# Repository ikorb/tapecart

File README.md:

# Tapecart SD #

This is a fork of tapecart that adds SD card support using the Tapuino hardware.
TCRT, PRG, and P00 files can be loaded using the Tapecart SD Browser (browser.prg) which should be placed in the root directory of the SD card.

Tapecart SD is not intended as a replacement for the Tapuino firmware, as there are no support for buttons and display
or using TAP files. Ideally, I would have preferred to use the original tapecart hardware and just replaced the SPI flash
with a SD card reader. However, the program flash in the microcontroller is too small for the FatFs library.

Flash and loader write commands are supported for TCRT files.

## Hardware ##

The Tapecart SD firmware should work on any Tapuino hardware.
For the tapecart LED this can be connected to the PD2 pin which is normally not used on a Tapuino.

There is also also this special version without buttons and display made for the Tapecart SD by CapFuture1975.
The gerber files for that version can be found under [hardware/Tapecart-SD](hardware/Tapecart-SD)

# tapecart #

tapecart - a tape port storage pod for the C64

Copyright (C) 2013-2017 by Ingo Korb <ingo@akana.de>
All rights reserved.
Idea by enthusi

# About #

The tapecart is a low-cost flash storage device for the Commodore 64's
tape port. This repository contains source code and documentation
related to it and will one day contain the schematics and layout files too.

# Structure of the repository #

This repository is organized as follows:

* doc

    This directory contains general documentation regarding the
    tapecart like the protocol it uses to communicate with the C64.

* src-c64

    This directory contains the source code for the C64-side
    software, currently the initial loader and the flashtool.

* sd_browser

    This directory contains the source code for the Tapecart SD Browser.

* src-firmware

    This directory contains the source code for the firmware running
    on the tapecart.

* hardware

    This directory contains schematics and layout for various hardware
    variants of the tapecart.

* mass-programmer

    This directory contains schematics, layout and software for a
    Raspberry Pi addon board that can be used for mass-programming
    tapecarts.

Schematics and layout for the tapecart itself will be released at a
later date.

# License #

The firmware itself is distributed under the following conditions:

    Redistribution and use in source and binary forms, with or without
    modification, are permitted provided that the following conditions
    are met:
    1. Redistributions of source code must retain the above copyright
       notice, this list of conditions and the following disclaimer.
    2. Redistributions in binary form must reproduce the above copyright
       notice, this list of conditions and the following disclaimer in the
       documentation and/or other materials provided with the distribution.

    THIS SOFTWARE IS PROVIDED BY THE REGENTS AND CONTRIBUTORS ``AS IS'' AND
    ANY EXPRESS OR IMPLIED WARRANTIES, INCLUDING, BUT NOT LIMITED TO, THE
    IMPLIED WARRANTIES OF MERCHANTABILITY AND FITNESS FOR A PARTICULAR PURPOSE
    ARE DISCLAIMED.  IN NO EVENT SHALL THE REGENTS OR CONTRIBUTORS BE LIABLE
    FOR ANY DIRECT, INDIRECT, INCIDENTAL, SPECIAL, EXEMPLARY, OR CONSEQUENTIAL
    DAMAGES (INCLUDING, BUT NOT LIMITED TO, PROCUREMENT OF SUBSTITUTE GOODS
    OR SERVICES; LOSS OF USE, DATA, OR PROFITS; OR BUSINESS INTERRUPTION)
    HOWEVER CAUSED AND ON ANY THEORY OF LIABILITY, WHETHER IN CONTRACT, STRICT
    LIABILITY, OR TORT (INCLUDING NEGLIGENCE OR OTHERWISE) ARISING IN ANY WAY
    OUT OF THE USE OF THIS SOFTWARE, EVEN IF ADVISED OF THE POSSIBILITY OF
    SUCH DAMAGE.

Please note that the firmware source code includes third-party header files
taken from the Atmel Software Framework. Please check its
[README](src-firmware/README.md) for more details.

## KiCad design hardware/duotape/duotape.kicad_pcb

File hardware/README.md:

# tapecart hardware #

This directory contains KiCAD schematics and layout for three
different implementations of the tapecart:

* DIY

    This version of the tapecart is optimized for DIY builders - it
    does not require any SMD components. Since DIP versions of the
    flash chips are a bit hard to source, it has an alternate
    footprint for using an SMD flash chip instead. The firmware for
    this version must be compiled using the config file "config-diy".
    A precompiled hex file is located in the subdirectory "firmware".

* SMD-Onesided-R1 and SMD-Twosided-R1

    These two versions of the tapecart are optimized for cost, using
    SMD components. Both are electrically the same, but one of them
    saves a bit more board space by placing components on both sides
    of the board. The firmware for both of these versions must be
    compiled using the config file "config-release1". A precompiled
    binary is located in the subdirectory "firmware".

* duotape and duotape-riser

    A simple tapecart-compatible tapeport switch, e.g. to switch
    between two tapecarts or a tapecart and a Datasette(-emulator).
    duotape is the main switch PCB, duotape-riser contains a layout
    for a really trivial adapter board in case you don't have a 3.96mm
    stripboard available.
    
# Tapecart SD hardware #

* Tapecart-SD

    A simple version of the Tapuino hardware without buttons and display
    specially made for Tapecart SD by CapFuture1975.

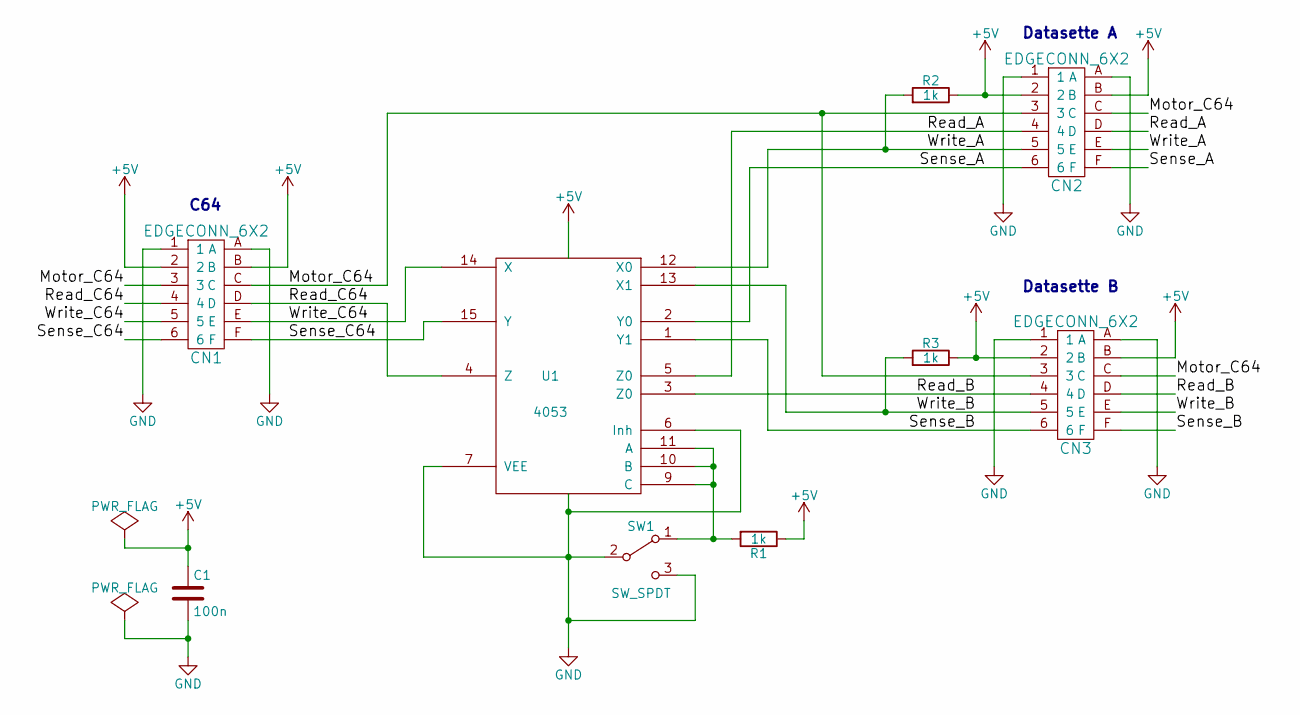
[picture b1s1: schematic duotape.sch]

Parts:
C1: 100n; C_Rect_L7_W2_P5
CN1, CN2: EDGECONN_6X2; EDGECONN_6x2_IMP
CN3: EDGECONN_6X2; VERTCONN_6X2
R1, R2, R3: 1k; Resistor_Horizontal_RM10mm
SW1: SW_SPDT; Switch_TL36P0
U1: 4053; DIP-16_W7.62mm

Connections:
+5V: C1.1, CN1.2, CN1.B, CN2.2, CN2.B, CN3.2, CN3.B, R1.1, R2.1, R3.1, U1.16 (VDD)
/Motor_C64: CN1.3, CN1.C, CN2.3, CN2.C, CN3.3, CN3.C
/Read_A: CN2.4, CN2.D, U1.5 (Z0)
/Read_B: CN3.4, CN3.D, U1.3 (Z0)
/Read_C64: CN1.4, CN1.D, U1.4 (Z)
/Sense_A: CN2.6, CN2.F, U1.2 (Y0)
/Sense_B: CN3.6, CN3.F, U1.1 (Y1)
/Sense_C64: CN1.6, CN1.F, U1.15 (Y)
/Write_A: CN2.5, CN2.E, R2.2, U1.12 (X0)
/Write_B: CN3.5, CN3.E, R3.2, U1.13 (X1)
/Write_C64: CN1.5, CN1.E, U1.14 (X)
GND: C1.2, CN1.1, CN1.A, CN2.1, CN2.A, CN3.1, CN3.A, SW1.2 (B), SW1.3 (C), U1.6 (Inh), U1.7 (VEE), U1.8 (VSS)
unnamed: R1.2, SW1.1 (A), U1.9 (C), U1.10 (B), U1.11 (A)

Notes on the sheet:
C64
Datasette A
Datasette B

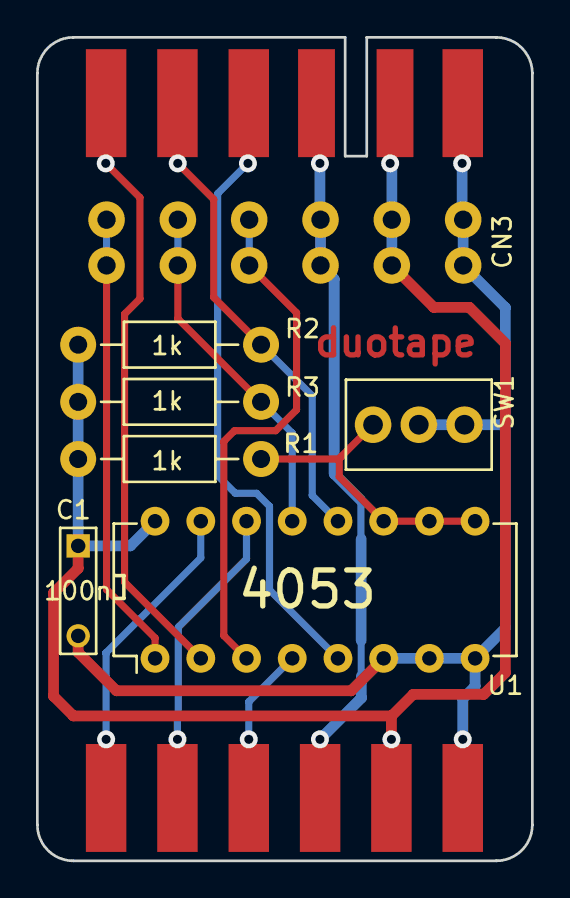
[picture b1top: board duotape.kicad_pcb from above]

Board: 2 copper layers, 27.5 x 45.8 mm, 9 parts (0 on the bottom side), 13 nets.

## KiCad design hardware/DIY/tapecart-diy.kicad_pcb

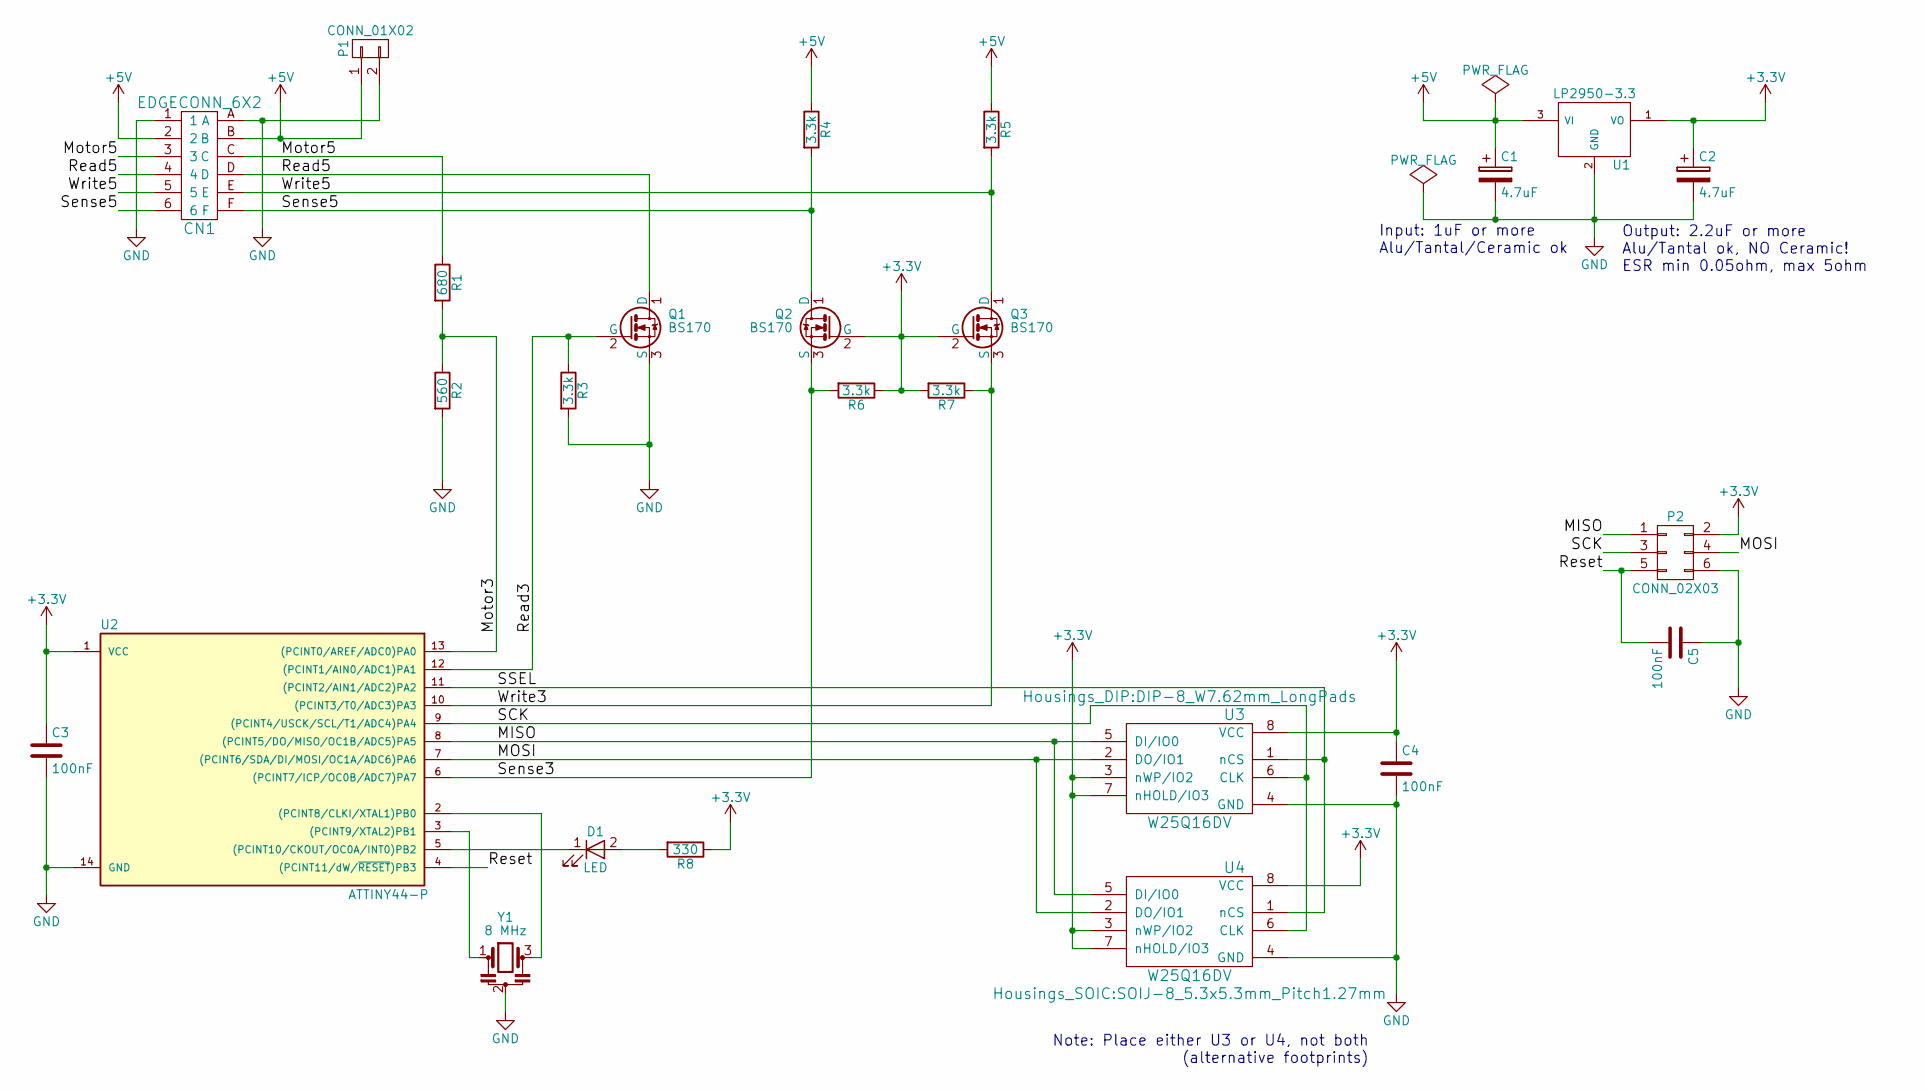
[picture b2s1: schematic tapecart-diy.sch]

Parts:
C1, C2: 4.7uF; C_Radial_D5_L11_P2
C3, C4, C5: 100nF; C_Disc_D3_P2.5
CN1: EDGECONN_6X2; EDGECONN_6x2_IMP_5mm
D1: LED; LED-3MM
P1: CONN_01X02; Pin_Header_Straight_1x02
P2: CONN_02X03; Pin_Header_Straight_2x03
Q1, Q2, Q3: BS170; TO-92_Inline_Wide
R1: 680; Resistor_Horizontal_RM10mm
R2: 560; Resistor_Horizontal_RM10mm
R3, R4, R5, R6, R7: 3.3k; Resistor_Horizontal_RM10mm
R8: 330; Resistor_Horizontal_RM10mm
U1: LP2950-3.3; TO-92_Inline_Wide
U2: ATTINY44-P; DIP-14_W7.62mm_LongPads
U3: W25Q16DV; DIP-8_W7.62mm_LongPads
U4: W25Q16DV; SOIJ-8_5.3x5.3mm_Pitch1.27mm
Y1: 8 MHz; Pin_Header_Straight_1x03

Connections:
+3V3: C2.1, C3.1, C4.1, P2.2, Q2.2 (G), Q3.2 (G), R6.1, R7.2, R8.1, U1.1 (VO), U2.1 (VCC), U3.3 (nWP/IO2), U3.7 (nHOLD/IO3), U3.8 (VCC), U4.3 (nWP/IO2), U4.7 (nHOLD/IO3), U4.8 (VCC)
+5V: C1.1, CN1.2, CN1.B, P1.1, R4.1, R5.1, U1.3 (VI)
/MISO: P2.1, U2.8 ((PCINT5/DO/MISO/OC1B/ADC5)PA5), U3.5 (DI/IO0), U4.5 (DI/IO0)
/MOSI: P2.4, U2.7 ((PCINT6/SDA/DI/MOSI/OC1A/ADC6)PA6), U3.2 (DO/IO1), U4.2 (DO/IO1)
/Motor3: R1.2, R2.1, U2.13 ((PCINT0/AREF/ADC0)PA0)
/Motor5: CN1.3, CN1.C, R1.1
/Read3: Q1.2 (G), R3.1, U2.12 ((PCINT1/AIN0/ADC1)PA1)
/Read5: CN1.4, CN1.D, Q1.1 (D)
/Reset: C5.2, P2.5, U2.4 ((PCINT11/dW/~RESET~)PB3)
/SCK: P2.3, U2.9 ((PCINT4/USCK/SCL/T1/ADC4)PA4), U3.6 (CLK), U4.6 (CLK)
/SSEL: U2.11 ((PCINT2/AIN1/ADC2)PA2), U3.1 (nCS), U4.1 (nCS)
/Sense3: Q2.3 (S), R6.2, U2.6 ((PCINT7/ICP/OC0B/ADC7)PA7)
/Sense5: CN1.6, CN1.F, Q2.1 (D), R4.2
/Write3: Q3.3 (S), R7.1, U2.10 ((PCINT3/T0/ADC3)PA3)
/Write5: CN1.5, CN1.E, Q3.1 (D), R5.2
GND: C1.2, C2.2, C3.2, C4.2, C5.1, CN1.1, CN1.A, P1.2, P2.6, Q1.3 (S), R2.2, R3.2, U1.2 (GND), U2.14 (GND), U3.4 (GND), U4.4 (GND), Y1.2
unnamed: D1.1 (K), U2.5 ((PCINT10/CKOUT/OC0A/INT0)PB2)
unnamed: D1.2 (A), R8.2
unnamed: U2.2 ((PCINT8/CLKI/XTAL1)PB0), Y1.3
unnamed: U2.3 ((PCINT9/XTAL2)PB1), Y1.1

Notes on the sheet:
Input: 1uF or more Alu/Tantal/Ceramic ok
Output: 2.2uF or more Alu/Tantal ok, NO Ceramic! ESR min 0.05ohm, max 5ohm
Note: Place either U3 or U4, not both (alternative footprints)

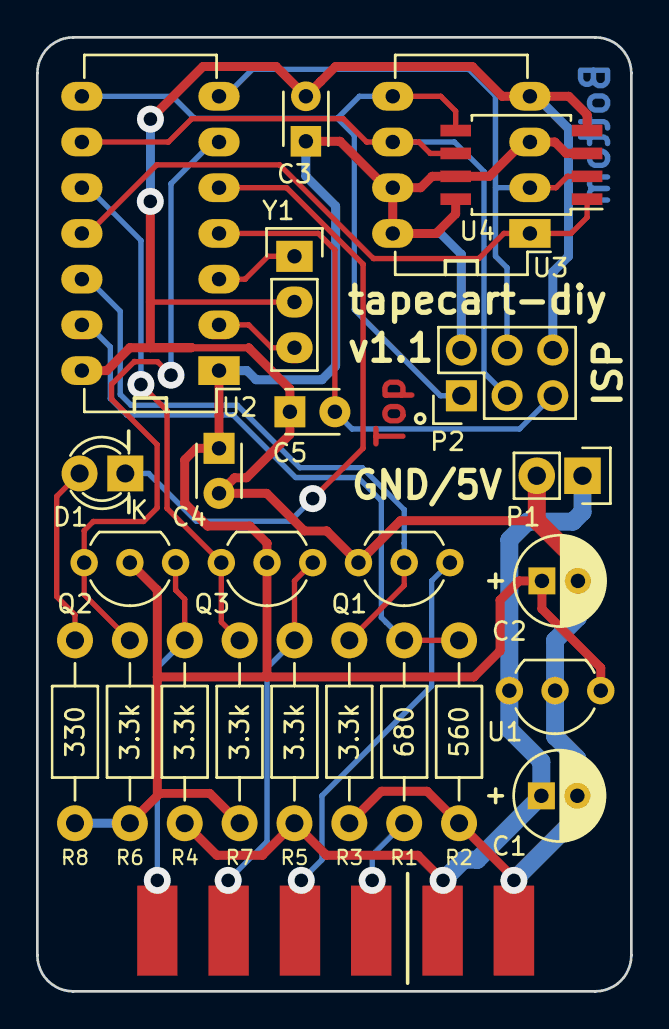
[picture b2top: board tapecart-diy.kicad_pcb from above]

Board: 2 copper layers, 33.0 x 53.0 mm, 25 parts (0 on the bottom side), 20 nets.

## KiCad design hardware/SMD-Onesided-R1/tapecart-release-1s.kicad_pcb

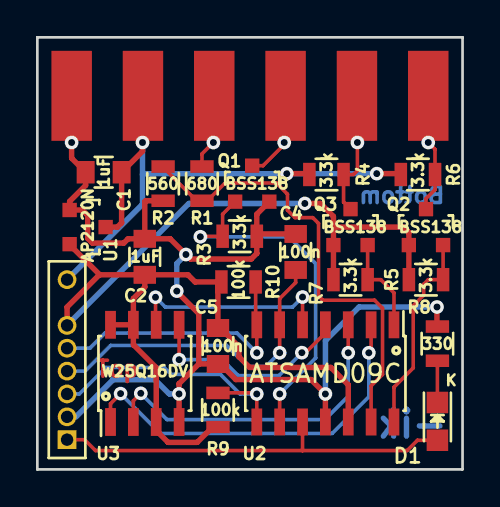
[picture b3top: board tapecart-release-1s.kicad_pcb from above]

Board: 2 copper layers, 23.6 x 24.0 mm, 23 parts (0 on the bottom side), 20 nets.

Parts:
C1, C2: 1uF; C_0805
C4, C5: 100n; C_0805
CN1: EDGECONN_6X2; EDGECONN_6x2_IMP_5mm
CN2: CONN_01X07; PINHEAD_6p1X1_1.27
D1: LED; LED_0805
Q1, Q2, Q3: BSS138; SOT-23
R1: 680; R_0805
R2: 560; R_0805
R3, R4, R5, R6, R7: 3.3k; R_0805
R8: 330; R_0805
R9, R10: 100k; R_0805
U1: AP2120N; SOT-23
U2: ATSAMD09C; SOIC-14_3.9x8.7mm_Pitch1.27mm
U3: W25Q16DV; SOIC-8_3.9x4.9mm_Pitch1.27mm

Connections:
+3V3: C2.1, C5.1, CN2.6, Q2.1, Q3.1, R5.1, R7.2, R9.1, R10.1, U1.2, U2.12, U3.3, U3.7, U3.8
+5V: C1.1, CN1.2, CN1.B, CN2.7, R4.1, R6.1, U1.3
/LED: CN2.1, D1.2, U2.10
/MISO: U2.3, U3.2
/MOSI: U2.4, U3.5
/Motor3: R1.2, R2.1, U2.13
/Motor5: CN1.3, CN1.C, R1.1
/Read3: Q1.1, R3.1, U2.9
/Read5: CN1.4, CN1.D, Q1.3
/Reset: C4.2, CN2.4, U2.6
/SCK: U2.5, U3.6
/SS: U2.2, U3.1
/SWCLK: CN2.5, R10.2, U2.7
/SWDIO: CN2.3, R9.2, U2.8
/Sense3: Q2.2, R5.2, U2.14
/Sense5: CN1.6, CN1.F, Q2.3, R6.2
/Write3: Q3.2, R7.1, U2.1
/Write5: CN1.5, CN1.E, Q3.3, R4.2
GND: C1.2, C2.2, C4.1, C5.2, CN1.1, CN1.A, CN2.2, Q1.2, R2.2, R3.2, R8.2, U1.1, U2.11, U3.4
unnamed: D1.1, R8.1

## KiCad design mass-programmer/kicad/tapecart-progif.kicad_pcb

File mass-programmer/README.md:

# tapecart mass programmer #

The tapecart mass programmer can be used to flash the firmware of a
newly-built tapecart and write data to its flash memory without
requiring a C64. It is implemented as an addon board for a Raspberry
Pi. Although in theory it should work with almost any version of the
Raspberry Pi, it has only been tested with a Raspberry Pi 2.

The finished programmer (without cable) looks like this:

## Hardware ##

The schematics and layout for the mass programmer are in the
[kicad](kicad) subdirectory. It includes a PDF version of the
schematic for easier previewing as well as pre-generated gerber files
suitable for fabrication. A BOM file in CSV format is included as
well.

To connect the programmer board to the tapecart, a cable with a 10-pin
2x5 connector on one end and an 8-pin 1.27mm pin header (pin 7
removed) on the other end is required. Since the pins on the 10-pin
connector and the 8-pin header are connected 1:1, the easiest way to
construct this is to use an IDC plug for the 10-pin side as the ribbon
cable has the same pin pitch as the 8-pin header on the other end. If
you do this, pin 7 on the cable will be unused as this pin must be
removed from the 8-pin header to ensure that it cannot be inserted the
wrong way. It is recommended to select a 1.27mm pin header with long
pins as they will have more flexibility, making better contact to the
plated vias on the tapecart's circuit board.

The mass programmer has two LEDs, a red and a green one. The red LED
indicates that the tapecart connected to the mass programmer is
currently powered. The green LED mirrors the state of the tapecart's
own LED, the programing software uses it to show that data is being
written.

The mass programmer-to-tapecart connection is designed to allow
hot-plugging - in fact, a tapecart must not be connected to it while
the Raspberry Pi boots as the GPIO pins may not be in the correct state.

## Software ##

To use the mass programmer, a Linux installation with a number of
additional software packages is needed on the Raspberry Pi - see the
section below for some notes how to install and configure a new
Raspbian system to meet these requirements.

The scripts used for controlling the mass programmer are in the
[scripts](scripts) subdirectory.

The most important script is ``prepare.sh``, which sets up the basic
configuration of the Raspberry's GPIO lines. It must be run again
every time the Raspberry Pi is booted and no tapecart must be
connected to the mass programmer before this script has been run!

The scripts ``poweron.sh`` and ``poweroff.sh`` turn the poer to the
tapecart on or off. If the power is on, the red LED on the mass
programmer board lights up. You must only connect or disconnect a
tapecart to the mass programmer while the red LED is off.

The script ``reset-to-uart.sh`` switches the tapecart into its remote
command mode, which is used to program it using the mass
programmer. It must be run before tcprog.rb can communicate with the
tapecart, but it can only work if the tapecart's microcontroller has
been programmed with its firmware using OpenOCD.

The program ``tcprog.rb`` is the main programming tool. It uses the
remote command mode to program the flash contents of the tapecart,
similar to the flashtool on the C64. Please use ``tcprog.rb --help``
to see a short summary of its command line options.

An example full-device programming script is included as
``massprog.sh``. It needs three arguments, the firmware binary, the
initial loader binary and a single-file PRG file which are written to
a tapecart. This process makes a just-assembled, blank tapecart ready
for use with a C64, but it can also be used to rewrite the data on an
already-programmed tapecart. Feel free to customize it as needed, for
example to leave out the firmware and loader programming steps is you
just want to rewrite the contents of a pre-programmed cart.

The firmware of the tapecart's microcontroller is programmed using a
sufficiently recent version of [OpenOCD](http://openocd.org). A
suitable ``openocd.conf`` can also be found in the [scripts](scripts)
subdirectory.

## Setting up Raspbian ##

Quick notes on setting up a Raspbian environment suitable for the mass
programmer, assuming that you know your way around a Linux command line:

* use [NOOBS](https://www.raspberrypi.org/downloads/noobs/) (or NOOBS
    Lite) to install a fresh copy of Raspbian (last tested using NOOBS
    version 2.0, but it should also work with later versions)
* disable the serial console by editing ``/boot/cmdline.txt``, remove
    the statement ``console=serial0,115200`` and reboot afterwards
* install a few required packages using ``sudo apt-get install
    libusb-1.0-0-dev libusb-dev gawk ruby-dev``
* install the serial port library for Ruby using ``gem install
    --user-install serialport``
* install a sufficiently-recent version of OpenOCD, meaning at least
    version 0.10.0 - the package in Raspbian is probably too old!

You can verify parts of the installation by running ``./tcprog.rb
--help`` - if it just shows the command line options, Ruby and the
required serialport library are working correctly.

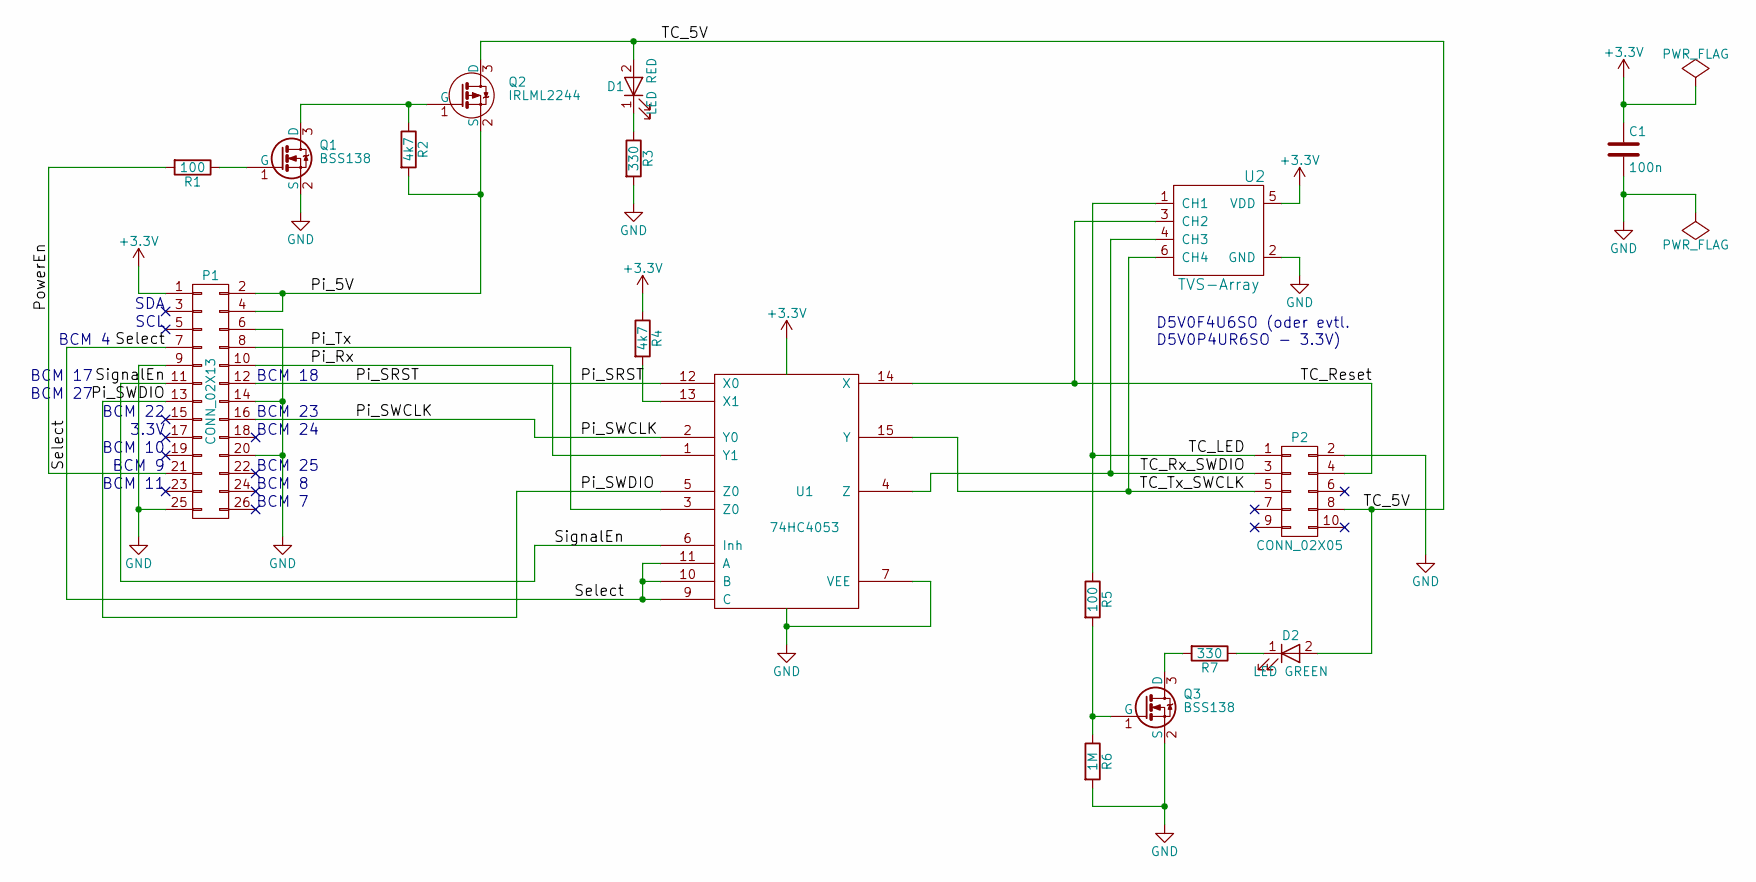
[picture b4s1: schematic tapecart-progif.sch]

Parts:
C1: 100n; C_0805
D1: LED RED; LED_0805
D2: LED GREEN; LED_0805
P1: CONN_02X13; Pin_Header_Straight_2x13
P2: CONN_02X05; IDC_Header_Straight_10pins
Q1, Q3: BSS138; SOT-23
Q2: IRLML2244; SOT-23
R1, R5: 100; R_0805
R2, R4: 4k7; R_0805
R3, R7: 330; R_0805
R6: 1M; R_0805
U1: 74HC4053; SOIC-16_3.9x9.9mm_Pitch1.27mm
U2: TVS-Array; SOT-23-6

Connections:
+3V3: C1.1, P1.1, R4.1, U1.16 (VDD), U2.5 (VDD)
/Pi_5V: P1.2, P1.4, Q2.2 (S), R2.2
/Pi_Rx: P1.10, U1.1 (Y1)
/Pi_SRST: P1.12, U1.12 (X0)
/Pi_SWCLK: P1.16, U1.2 (Y0)
/Pi_SWDIO: P1.13, U1.5 (Z0)
/Pi_Tx: P1.8, U1.3 (Z0)
/PowerEn: P1.21, R1.2
/Select: P1.7, U1.9 (C), U1.10 (B), U1.11 (A)
/SignalEn: P1.11, U1.6 (Inh)
/TC_5V: D1.2 (A), D2.2 (A), P2.8, Q2.3 (D)
/TC_LED: P2.1, R5.1, U2.1 (CH1)
/TC_Reset: P2.4, U1.14 (X), U2.3 (CH2)
/TC_Rx_SWDIO: P2.3, U1.4 (Z), U2.4 (CH3)
/TC_Tx_SWCLK: P2.5, U1.15 (Y), U2.6 (CH4)
GND: C1.2, P1.6, P1.9, P1.14, P1.20, P1.25, P2.2, Q1.2 (S), Q3.2 (S), R3.2, R6.2, U1.7 (VEE), U1.8 (VSS), U2.2 (GND)
unnamed: D1.1 (K), R3.1
unnamed: D2.1 (K), R7.1
unnamed: Q1.1 (G), R1.1
unnamed: Q1.3 (D), Q2.1 (G), R2.1
unnamed: Q3.1 (G), R5.2, R6.1
unnamed: Q3.3 (D), R7.2
unnamed: R4.2, U1.13 (X1)

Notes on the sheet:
D5V0F4U6SO (oder evtl. D5V0P4UR6SO - 3.3V)
SDA
SCL
BCM 27
BCM 17
BCM 22
3.3V
BCM 10
BCM 9
BCM 11
BCM 7
BCM 8
BCM 23
BCM 4
BCM 25
BCM 24
BCM 18

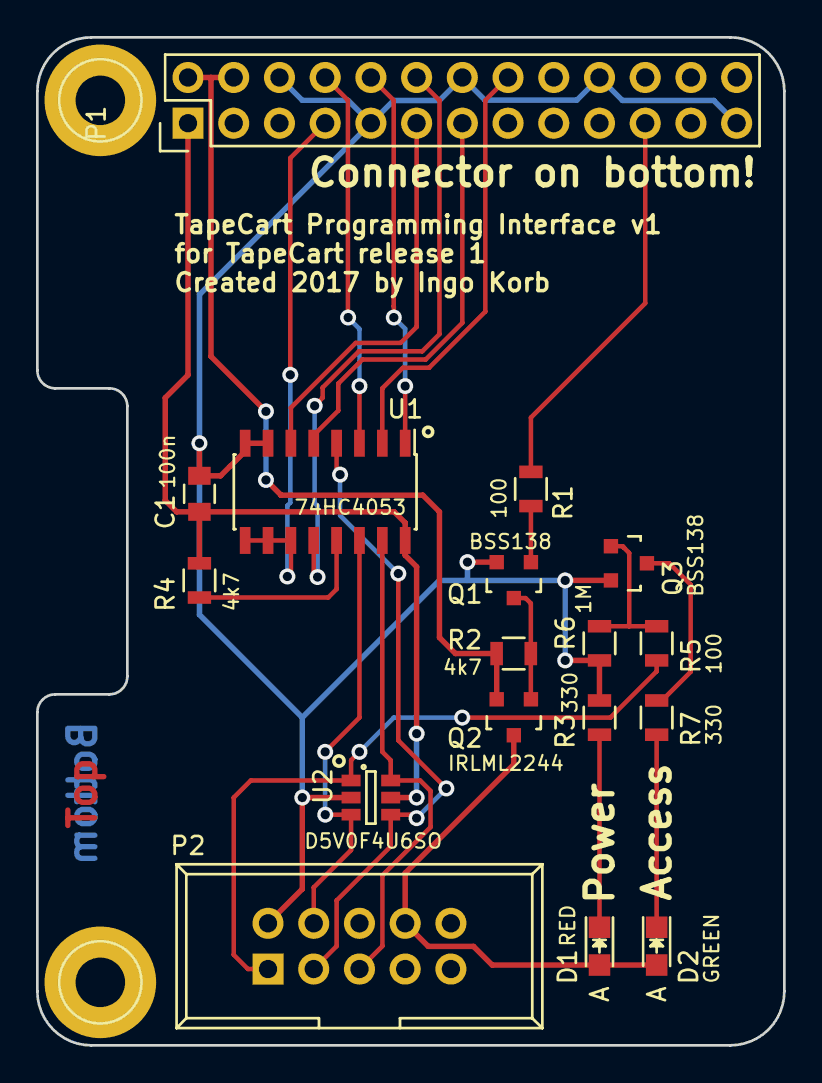
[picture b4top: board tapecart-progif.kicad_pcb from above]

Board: 2 copper layers, 41.5 x 56.0 mm, 19 parts (0 on the bottom side), 23 nets.

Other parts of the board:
HOLE1, HOLE2: 1pin

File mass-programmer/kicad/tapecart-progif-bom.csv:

Reference, Value, Footprint, Notes
"C1","100n","Capacitors_SMD:C_0805",""
"D1","LED RED","LEDs:LED_0805",""
"D2","LED GREEN","LEDs:LED_0805",""
"P1","CONN_02X13","Pin_Headers:Pin_Header_Straight_2x13",""
"P2","CONN_02X05","Connect:IDC_Header_Straight_10pins",""
"Q1","BSS138","TO_SOT_Packages_SMD:SOT-23",""
"Q2","IRLML2244","TO_SOT_Packages_SMD:SOT-23",""
"Q3","BSS138","TO_SOT_Packages_SMD:SOT-23",""
"R1","100","Resistors_SMD:R_0805",""
"R2","4k7","Resistors_SMD:R_0805",""
"R3","330","Resistors_SMD:R_0805",""
"R4","4k7","Resistors_SMD:R_0805",""
"R5","100","Resistors_SMD:R_0805",""
"R6","1M","Resistors_SMD:R_0805",""
"R7","330","Resistors_SMD:R_0805",""
"U1","74HC4053","Housings_SOIC:SOIC-16_3.9x9.9mm_Pitch1.27mm",""
"U2","D5V0F4U6SO","TO_SOT_Packages_SMD:SOT-23-6","or D5V0P4UR6SO or similar (original type was 5V because of availability)"

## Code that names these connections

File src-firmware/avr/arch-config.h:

/* tapecart - a tape port storage pod for the C64

   Copyright (C) 2013-2017  Ingo Korb <ingo@akana.de>
   All rights reserved.
   Idea by enthusi

   Redistribution and use in source and binary forms, with or without
   modification, are permitted provided that the following conditions
   are met:
   1. Redistributions of source code must retain the above copyright
      notice, this list of conditions and the following disclaimer.
   2. Redistributions in binary form must reproduce the above copyright
      notice, this list of conditions and the following disclaimer in the
      documentation and/or other materials provided with the distribution.

   THIS SOFTWARE IS PROVIDED BY THE REGENTS AND CONTRIBUTORS ``AS IS'' AND
   ANY EXPRESS OR IMPLIED WARRANTIES, INCLUDING, BUT NOT LIMITED TO, THE
   IMPLIED WARRANTIES OF MERCHANTABILITY AND FITNESS FOR A PARTICULAR PURPOSE
   ARE DISCLAIMED.  IN NO EVENT SHALL THE REGENTS OR CONTRIBUTORS BE LIABLE
   FOR ANY DIRECT, INDIRECT, INCIDENTAL, SPECIAL, EXEMPLARY, OR CONSEQUENTIAL
   DAMAGES (INCLUDING, BUT NOT LIMITED TO, PROCUREMENT OF SUBSTITUTE GOODS
   OR SERVICES; LOSS OF USE, DATA, OR PROFITS; OR BUSINESS INTERRUPTION)
   HOWEVER CAUSED AND ON ANY THEORY OF LIABILITY, WHETHER IN CONTRACT, STRICT
   LIABILITY, OR TORT (INCLUDING NEGLIGENCE OR OTHERWISE) ARISING IN ANY WAY
   OUT OF THE USE OF THIS SOFTWARE, EVEN IF ADVISED OF THE POSSIBILITY OF
   SUCH DAMAGE.


   arch-config.h: Architecture-specific configuration stuff

*/


#ifndef ARCH_CONFIG_H
#define ARCH_CONFIG_H

#include <avr/io.h>
#include <avr/pgmspace.h>

/* I/O port definitions */
/* note: Write and Sense must be on the same port */
#if CONFIG_HARDWARE_VARIANT != 5

#define SENSE_PORT  PORTA
#define SENSE_DDR   DDRA
#define SENSE_PIN   PINA

#define WRITE_PORT  PORTA
#define WRITE_DDR   DDRA
#define WRITE_PIN   PINA

#define READ_PORT   PORTA
#define READ_DDR    DDRA
#define READ_PIN    PINA

#define MOTOR_PORT  PORTA
#define MOTOR_DDR   DDRA
#define MOTOR_PIN   PINA

#define LED_PORT    PORTB
#define LED_DDR     DDRB
#define LED_BIT     2

#define MOTOR_BIT   0
#define MOTOR_VECT  PCINT0_vect

#endif

/* early prototypes with I2C-EEPROM */
#if CONFIG_HARDWARE_VARIANT == 1
#  define SENSE_BIT   1
#  define WRITE_BIT   7
#  define READ_BIT    5

#  define MOTOR_INVERTED
#  define LED_ACTIVE_LOW


/* late prototypes with AT45 */
#elif CONFIG_HARDWARE_VARIANT == 2
#  define SENSE_BIT 7
#  define WRITE_BIT 3
#  define READ_BIT  1

#  define MOTOR_INVERTED
#  define LED_ACTIVE_LOW


/* tapecart-diy */
#elif CONFIG_HARDWARE_VARIANT == 4
#  define SENSE_BIT 7
#  define WRITE_BIT 3
#  define READ_BIT  1

#  define READ_INVERTED
#  define LED_ACTIVE_LOW

/* tapecart-tapuino */
#elif CONFIG_HARDWARE_VARIANT == 5

#define SENSE_PORT  PORTD
#define SENSE_DDR   DDRD
#define SENSE_PIN   PIND
#define SENSE_BIT   5

#define WRITE_PORT  PORTB
#define WRITE_DDR   DDRB
#define WRITE_PIN   PINB
#define WRITE_BIT   0

#define READ_PORT   PORTD
#define READ_DDR    DDRD
#define READ_PIN    PIND
#define READ_BIT    3

#define MOTOR_PORT  PORTD
#define MOTOR_DDR   DDRD
#define MOTOR_PIN   PIND
#define MOTOR_BIT   4
#define MOTOR_VECT  PCINT2_vect

/* NOTE: Normally not connected on Tapuino */
#define LED_PORT    PORTD
#define LED_DDR     DDRD
#define LED_BIT     2

#define MOTOR_INVERTED

#define HAVE_UART

#else
#  error "Unknown hardware variant selected"
#endif


#ifdef HAVE_I2C

#  define SOFTI2C_PORT    PORTA
#  define SOFTI2C_DDR     DDRA
#  define SOFTI2C_PIN     PINA
#  define SOFTI2C_BIT_SDA 2
#  define SOFTI2C_BIT_SCL 3

// Half-clock-period delay, minimum 3
#  define SOFTI2C_DELAY 3

/* external EEPROM */
#  define EEPROM_ADDR      0xa0

#elif defined(HAVE_AT45) || defined(HAVE_W25Q)

#  define SPI_PORT  PORTA
#  define SPI_DDR   DDRA
#  define SPI_SS    PA2
#  define SPI_SCK   PA4
#  define SPI_DO    PA5
#  define SPI_DI    PA6

#elif defined(HAVE_SD)

#  define SPI_PORT  PORTB
#  define SPI_DDR   DDRB
#  define SPI_SS    PB2
#  define SPI_SCK   PB5
#  define SPI_DO    PB3
#  define SPI_DI    PB4

#else

#  error "Unknown memory type specified"

#endif

static inline void ioport_init(void) {
  WRITE_PORT &= ~_BV(WRITE_BIT); // we have an external pullup
  WRITE_DDR  &= ~_BV(WRITE_BIT);
  READ_PORT  &= ~_BV(READ_BIT);
  READ_DDR   |=  _BV(READ_BIT);
  MOTOR_PORT |=  _BV(MOTOR_BIT);
  MOTOR_DDR  &= ~_BV(MOTOR_BIT);
  SENSE_PORT &= ~_BV(SENSE_BIT);
  SENSE_DDR  |=  _BV(SENSE_BIT);
#ifdef LED_ACTIVE_LOW
  LED_PORT   |=  _BV(LED_BIT);
  LED_DDR    &= ~_BV(LED_BIT);
#else
  LED_PORT   &= ~_BV(LED_BIT);
  LED_DDR    |=  _BV(LED_BIT);
#endif

  /* motor PCINT */
#if CONFIG_HARDWARE_VARIANT != 5

  PCMSK0  = _BV(MOTOR_BIT);
  GIMSK  |= _BV(PCIE0);
  GIFR   |= _BV(PCIF0);

#else

  PCMSK2  = _BV(MOTOR_BIT);
  PCICR  |= _BV(PCIE2);
  PCIFR  |= _BV(PCIF2);

#endif
}

static inline void ioport_uart_init(void) { }

typedef __uint24 uint24;

#define FLASH __flash
#define FLASH_MEMCPY memcpy_P

#define EEMEM

#endif

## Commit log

2016-12-29 Import Tapecart firmware sources
2016-12-30 Add C64 flashtool sources
2016-12-30 Add a bit of documentation
2016-12-30 Add main README file
2016-12-30 Remove stray space from progref
2017-01-02 Add missing word
2017-01-14 Add color coding to make non-default loader more noticable
2017-01-14 Ensure that the device address used by flashtool is valid
2017-01-26 Update copyright notices for 2017
2017-01-29 flashtool: UI improvements
    Add a few UI improvements to the flashtool:
    - show selected function as centered heading
    - show current device number in lower status bar
    - pre-fill fields in bootfile location function
    - show answer of "Use basic starter" question in onefiler writing
2017-01-29 flashtool: Variable cleanup
2017-01-29 flashtool: Move some functions to an "advanced" submenu
2017-01-29 flashtool: Add functions to dump loader/flash
2017-01-29 flashtool: Add load address to dumped loader
    Add the default load address of 0x0351 to a dumped loader for
    consistency with the "Write custom loader" function.
2017-01-31 Add TCRT documentation and support for it in flashtool
    Add documentation for the TCRT file format, which is intended to store
    the full memory state of a tapecart in a file, e.g. as serialisation
    format in an emulator or as distribution format for programs that run
    from a tapecart. Implement writing and dumping of that format in flashtool.
2017-01-31 flashtool: Recognize stop key as cancel at prompts
2017-01-31 flashtool: Move call address prompt down one line
2017-01-31 flashtool: Bump version number to 1.1
2017-01-31 flashtool: Add timeout to tapecart detection
    Add a ~5 second timeout to tapecart_cmdmode and complain about a
    missing tapecart if that timeout is reached.
2017-04-15 Add mass programming interface
2017-05-12 Fix short description in header of tcrt.c
    Fix a copy-and-paste error in the header comment of tcrt.c
2017-05-12 Add specs for a data block offset
    Update the programmer's reference and TCRT specification with an
    option to launch a program with a data block offset to allow sharing a
    tapecart between multiple applications.
2017-05-27 Fix link in doc/README.md
2017-05-27 tcprog.rb: Add option to specify data offset
2017-05-29 tcprog.rb: Set baud rate separately
2017-08-09 REU support
2017-08-10 Revert "flashtool: Add timeout to tapecart detection"
    This reverts commit 2edab8821b16d5c08c49c26bec473171d1a79ac0.
2017-08-12 Workaround for REU bug
2017-08-13 flashtool: Increase detection timeout to a more reasonable level
2017-08-13 Remove obsolete and misleading comments from loader
2017-08-13 Add support for reading files from a REU
2017-08-13 io.h/io.c: Fix code style
2017-08-13 flashtool: Fix ignored offset in hexdump function
2017-08-13 flashtool: Swap "write onefiler"/"write TCRT" menu entries
    Since it is likely that people will write more TCRTs than onefilers to
    their tapecart, move the more common option to the top so it becomes
    the default.
2017-08-13 flashtool: Allow longer file names
    Extent the string input code and widen all file name entry fields to
    allow longer file names, e.g. to specify a CMD-compatible path name.
2017-08-13 flashtool: Implement a rudimentary drive menu
2017-08-13 flashtool: Access REU with device number 0
    Change the REU access method from a magic file name to device number 0
    to improve discoverability.
2017-08-13 flashtool: Implement Home/End keys for string inputs
    Implement Home and End (Shift-Home) keys for moving to the beginning
    or end of a string input field.
2017-08-13 flashtool: Fix vertical position of some commands
2017-08-13 flashtool: Bump version number to 1.2
2017-11-05 Add directory lister to flashtool drive menu
2017-11-05 Add tapecart-diy support to firmware
2017-11-08 Add schematics and layout files
2017-12-24 Add duotape, a two-port tapeport switcher
2017-12-26 ProgRef: Add note about reading/writing beyond end of flash
2017-12-26 Fix typo in READ_CAPABILITIES command name
2019-03-22 Set end of array variables after load
2019-03-22 Add support for SD card
2019-06-07 remove obsolete files
2019-11-28 Update spi_init. Outputs high at start-up and no clock
2019-11-28 Use slower clock for SPI init and add spi_disable
2019-12-18 Fix SD card init problem that occur with some adapters
2020-01-26 Always load browser from root dir
2020-01-26 Use home key for root directory
2020-01-30 Add Tapecart SD gerbers by CapFuture1975
2020-01-30 Fix link
2022-01-13 Only try to load PRG and TCRT files
2022-01-13 Convert filenames to PETSCII
2022-01-13 Allow to select SID files
2022-01-15 Support P00 files
2022-01-15 Add P00 files
2022-01-31 fix writing of non-multiple-of-page-size tcrt files
2022-01-31 fix screen layout error when writing tcrt
2022-01-31 update flashtool version number and NEWS file
2022-02-09 Add TCRT write support
2022-12-29 separate cart status update from status printing
2022-12-29 send initialize after eload drive detection
    Initialize drive after using eload's drive type detection, seems to
    avoid occasional "DISK ID MISMATCH" errors.
2022-12-29 avoid overflowing numeric input fields
2022-12-29 show current menu/function in top status bar
2022-12-29 flashtool: Bump version number to 1.3
2022-12-29 add eload fastloader
2022-12-29 Use optimized block write for writing to flash
2022-12-29 add a TUI file selector
    Use a nice TUI file selector instead of blind text input fields for
    selecting files to flash.
2022-12-29 shrink cart status by one line
2022-12-29 use global vars for some loop counters
2022-12-29 Measure elapsed time while writing to flash
